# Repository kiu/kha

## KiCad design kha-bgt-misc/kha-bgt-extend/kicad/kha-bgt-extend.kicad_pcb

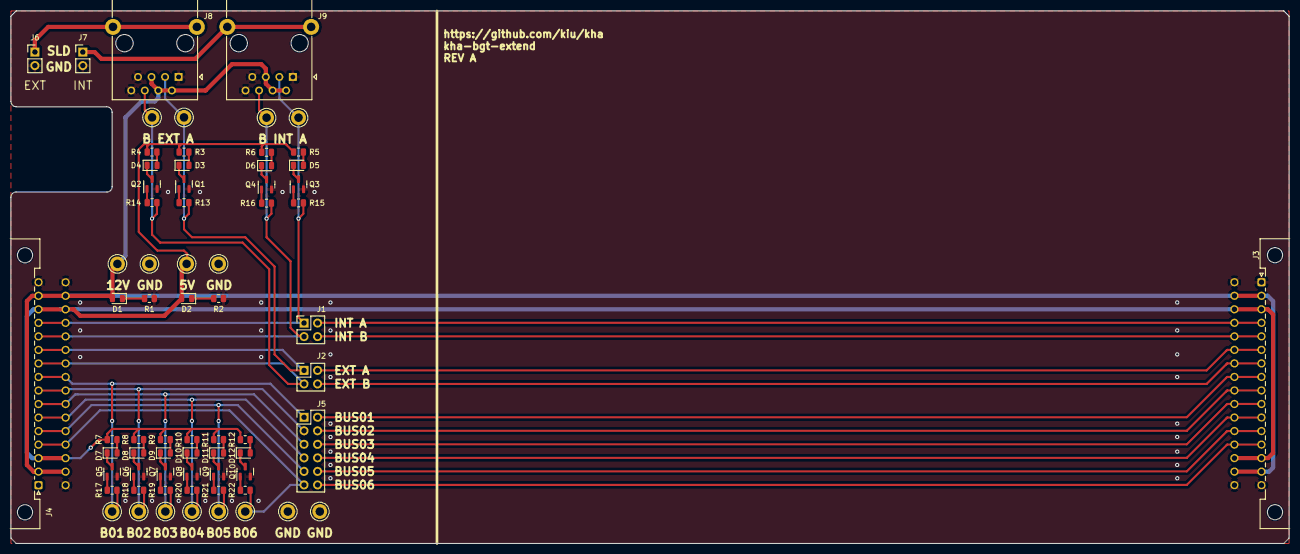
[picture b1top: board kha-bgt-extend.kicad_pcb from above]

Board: 2 copper layers, 240.0 x 100.0 mm, 69 parts (0 on the bottom side), 57 nets.

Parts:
D1, D2: green; LED_0805_2012Metric
D3, D4, D5, D6, D7, D8, D9, D10, D11, D12: yellow; LED_0805_2012Metric
J1, J2: Conn_02x02_Odd_Even; PinHeader_2x02_P2.54mm_Vertical
J3, J4: DIN41612_02x16_AC; DIN41612_C2_2x16_Male_Horizontal_THT
J5: Conn_02x06_Odd_Even; PinHeader_2x06_P2.54mm_Vertical
J6, J7: Conn_01x02; PinHeader_1x02_P2.54mm_Vertical
J8, J9: RJ45_Shielded; GDLX-S-88K
Q1, Q2, Q3, Q4, Q5, Q6, Q7, Q8, Q9, Q10: DMG2302U; SOT-23
R1, R2, R3, R4, R5, R6, R7, R8, R9, R10, R11, R12: R; R_0805_2012Metric
R13, R14, R15, R16, R17, R18, R19, R20, R21, R22: 10R; R_0805_2012Metric
TP1, TP2, TP3, TP4, TP5, TP6, TP7, TP8, TP9, TP10, TP11, TP12, TP13, TP14, TP15, TP16: TestPoint; TestPoint_Keystone_5010-5014_Multipurpose

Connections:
+5V: D2.2 (A), J3.a3, J3.a14, J3.c3, J3.c14, J4.a3, J4.a14, J4.c3, J4.c14, R3.2, R4.2, R5.2, R6.2, R7.2, R8.2, R9.2, R10.2, R11.2, R12.2, TP2.1
+12V: D1.2 (A), J3.a2, J3.a15, J3.c2, J3.c15, J4.a2, J4.a15, J4.c2, J4.c15, J8.2, J8.4, J8.5, J9.2, J9.4, J9.5, TP1.1
C_BUS01: J4.a9, J4.c9, J5.1, R17.2, TP11.1
C_BUS02: J4.a8, J4.c8, J5.3, R18.2, TP12.1
C_BUS03: J4.a7, J4.c7, J5.5, R19.2, TP13.1
C_BUS04: J4.a6, J4.c6, J5.7, R20.2, TP14.1
C_BUS05: J4.a5, J4.c5, J5.9, R21.2, TP15.1
C_BUS06: J4.a4, J4.c4, J5.11, R22.2, TP16.1
C_RS485_A: J2.1, J4.a11, J4.c11, J8.3, R13.2, TP7.1
C_RS485_B: J2.3, J4.a10, J4.c10, J8.6, R14.2, TP8.1
C_RS485_INT_A: J1.1, J4.a13, J4.c13, J9.3, R15.2, TP9.1
C_RS485_INT_B: J1.3, J4.a12, J4.c12, J9.6, R16.2, TP10.1
GND: J3.a1, J3.a16, J3.c1, J3.c16, J4.a16, J4.c1, J4.c16, J6.2, J7.2, J8.1, J8.7, J8.8, J9.1, J9.7, J9.8, Q1.2 (S), Q2.2 (S), Q3.2 (S), Q4.2 (S), Q5.2 (S), Q6.2 (S), Q7.2 (S), Q8.2 (S), Q9.2 (S), Q10.2 (S), R1.1, R2.1, TP3.1, TP4.1, TP5.1, TP6.1
unnamed: D1.1 (K), R1.2
unnamed: D2.1 (K), R2.2
unnamed: D3.2 (A), R3.1
unnamed: D3.1 (K), Q1.3 (D)
unnamed: D4.2 (A), R4.1
unnamed: D4.1 (K), Q2.3 (D)
unnamed: D5.2 (A), R5.1
unnamed: D5.1 (K), Q3.3 (D)
unnamed: D6.2 (A), R6.1
unnamed: D6.1 (K), Q4.3 (D)
unnamed: D7.2 (A), R7.1
unnamed: D7.1 (K), Q5.3 (D)
unnamed: D8.2 (A), R8.1
unnamed: D8.1 (K), Q6.3 (D)
unnamed: D9.2 (A), R9.1
unnamed: D9.1 (K), Q7.3 (D)
unnamed: D10.2 (A), R10.1
unnamed: D10.1 (K), Q8.3 (D)
unnamed: D11.2 (A), R11.1
unnamed: D11.1 (K), Q9.3 (D)
unnamed: D12.2 (A), R12.1
unnamed: D12.1 (K), Q10.3 (D)
unnamed: J6.1, J8.SH
unnamed: J7.1, J9.SH
unnamed: Q1.1 (G), R13.1
unnamed: Q2.1 (G), R14.1
unnamed: Q3.1 (G), R15.1
unnamed: Q4.1 (G), R16.1
unnamed: Q5.1 (G), R17.1
unnamed: Q6.1 (G), R18.1
unnamed: Q7.1 (G), R19.1
unnamed: Q8.1 (G), R20.1
unnamed: Q9.1 (G), R21.1
unnamed: Q10.1 (G), R22.1
R_BUS01: J3.a8, J3.c8, J5.2
R_BUS02: J3.a9, J3.c9, J5.4
R_BUS03: J3.a10, J3.c10, J5.6
R_BUS04: J3.a11, J3.c11, J5.8
R_BUS05: J3.a12, J3.c12, J5.10
R_BUS06: J3.a13, J3.c13, J5.12
R_RS485_A: J2.2, J3.a6, J3.c6
R_RS485_B: J2.4, J3.a7, J3.c7
R_RS485_INT_A: J1.2, J3.a4, J3.c4
R_RS485_INT_B: J1.4, J3.a5, J3.c5

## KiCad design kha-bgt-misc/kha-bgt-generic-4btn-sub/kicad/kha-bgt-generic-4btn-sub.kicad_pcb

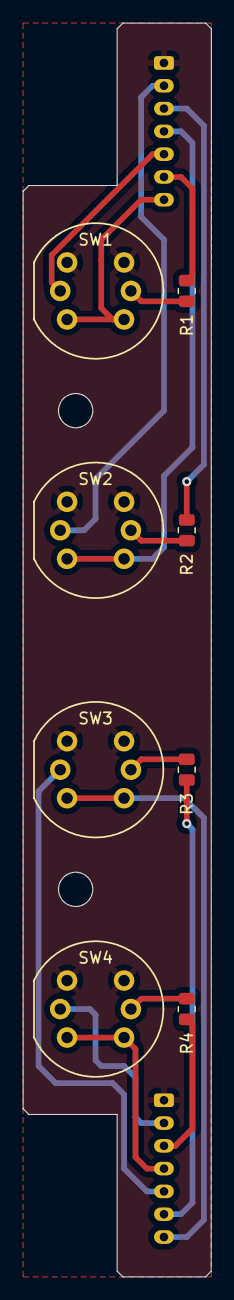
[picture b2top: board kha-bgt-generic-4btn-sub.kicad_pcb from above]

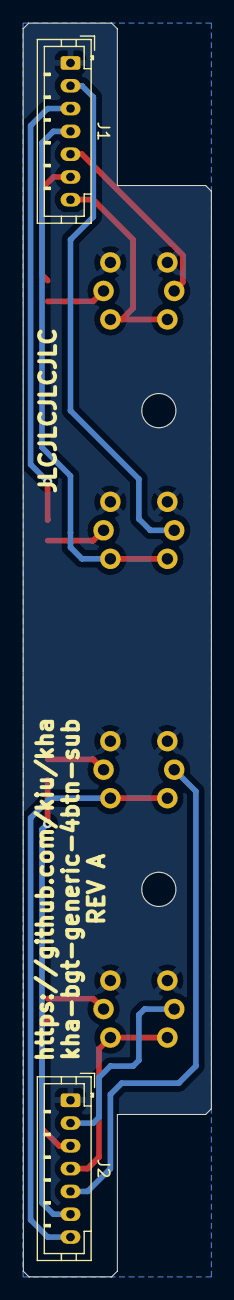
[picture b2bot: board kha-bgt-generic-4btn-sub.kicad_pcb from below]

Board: 2 copper layers, 16.5 x 110.0 mm, 10 parts (2 on the bottom side), 17 nets.

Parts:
J1, J2: Conn_01x07; JST_PH_B7B-PH-K_1x07_P2.00mm_Vertical
R1, R2, R3, R4: R; R_0805_2012Metric
SW1, SW2, SW3, SW4: KS01-BL

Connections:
GND: J1.1, J2.1, SW1.2, SW2.2, SW3.2, SW4.2
unnamed: J1.2, SW2.6
unnamed: J1.3, R2.1
unnamed: J1.4, SW2.1
unnamed: J1.5, SW1.6
unnamed: J1.6, R1.1
unnamed: J1.7, SW1.1
unnamed: J2.2, SW4.6
unnamed: J2.3, R4.1
unnamed: J2.4, SW4.1
unnamed: J2.5, SW3.6
unnamed: J2.6, R3.1
unnamed: J2.7, SW3.1
unnamed: R1.2, SW1.5
unnamed: R2.2, SW2.5
unnamed: R3.2, SW3.5
unnamed: R4.2, SW4.5

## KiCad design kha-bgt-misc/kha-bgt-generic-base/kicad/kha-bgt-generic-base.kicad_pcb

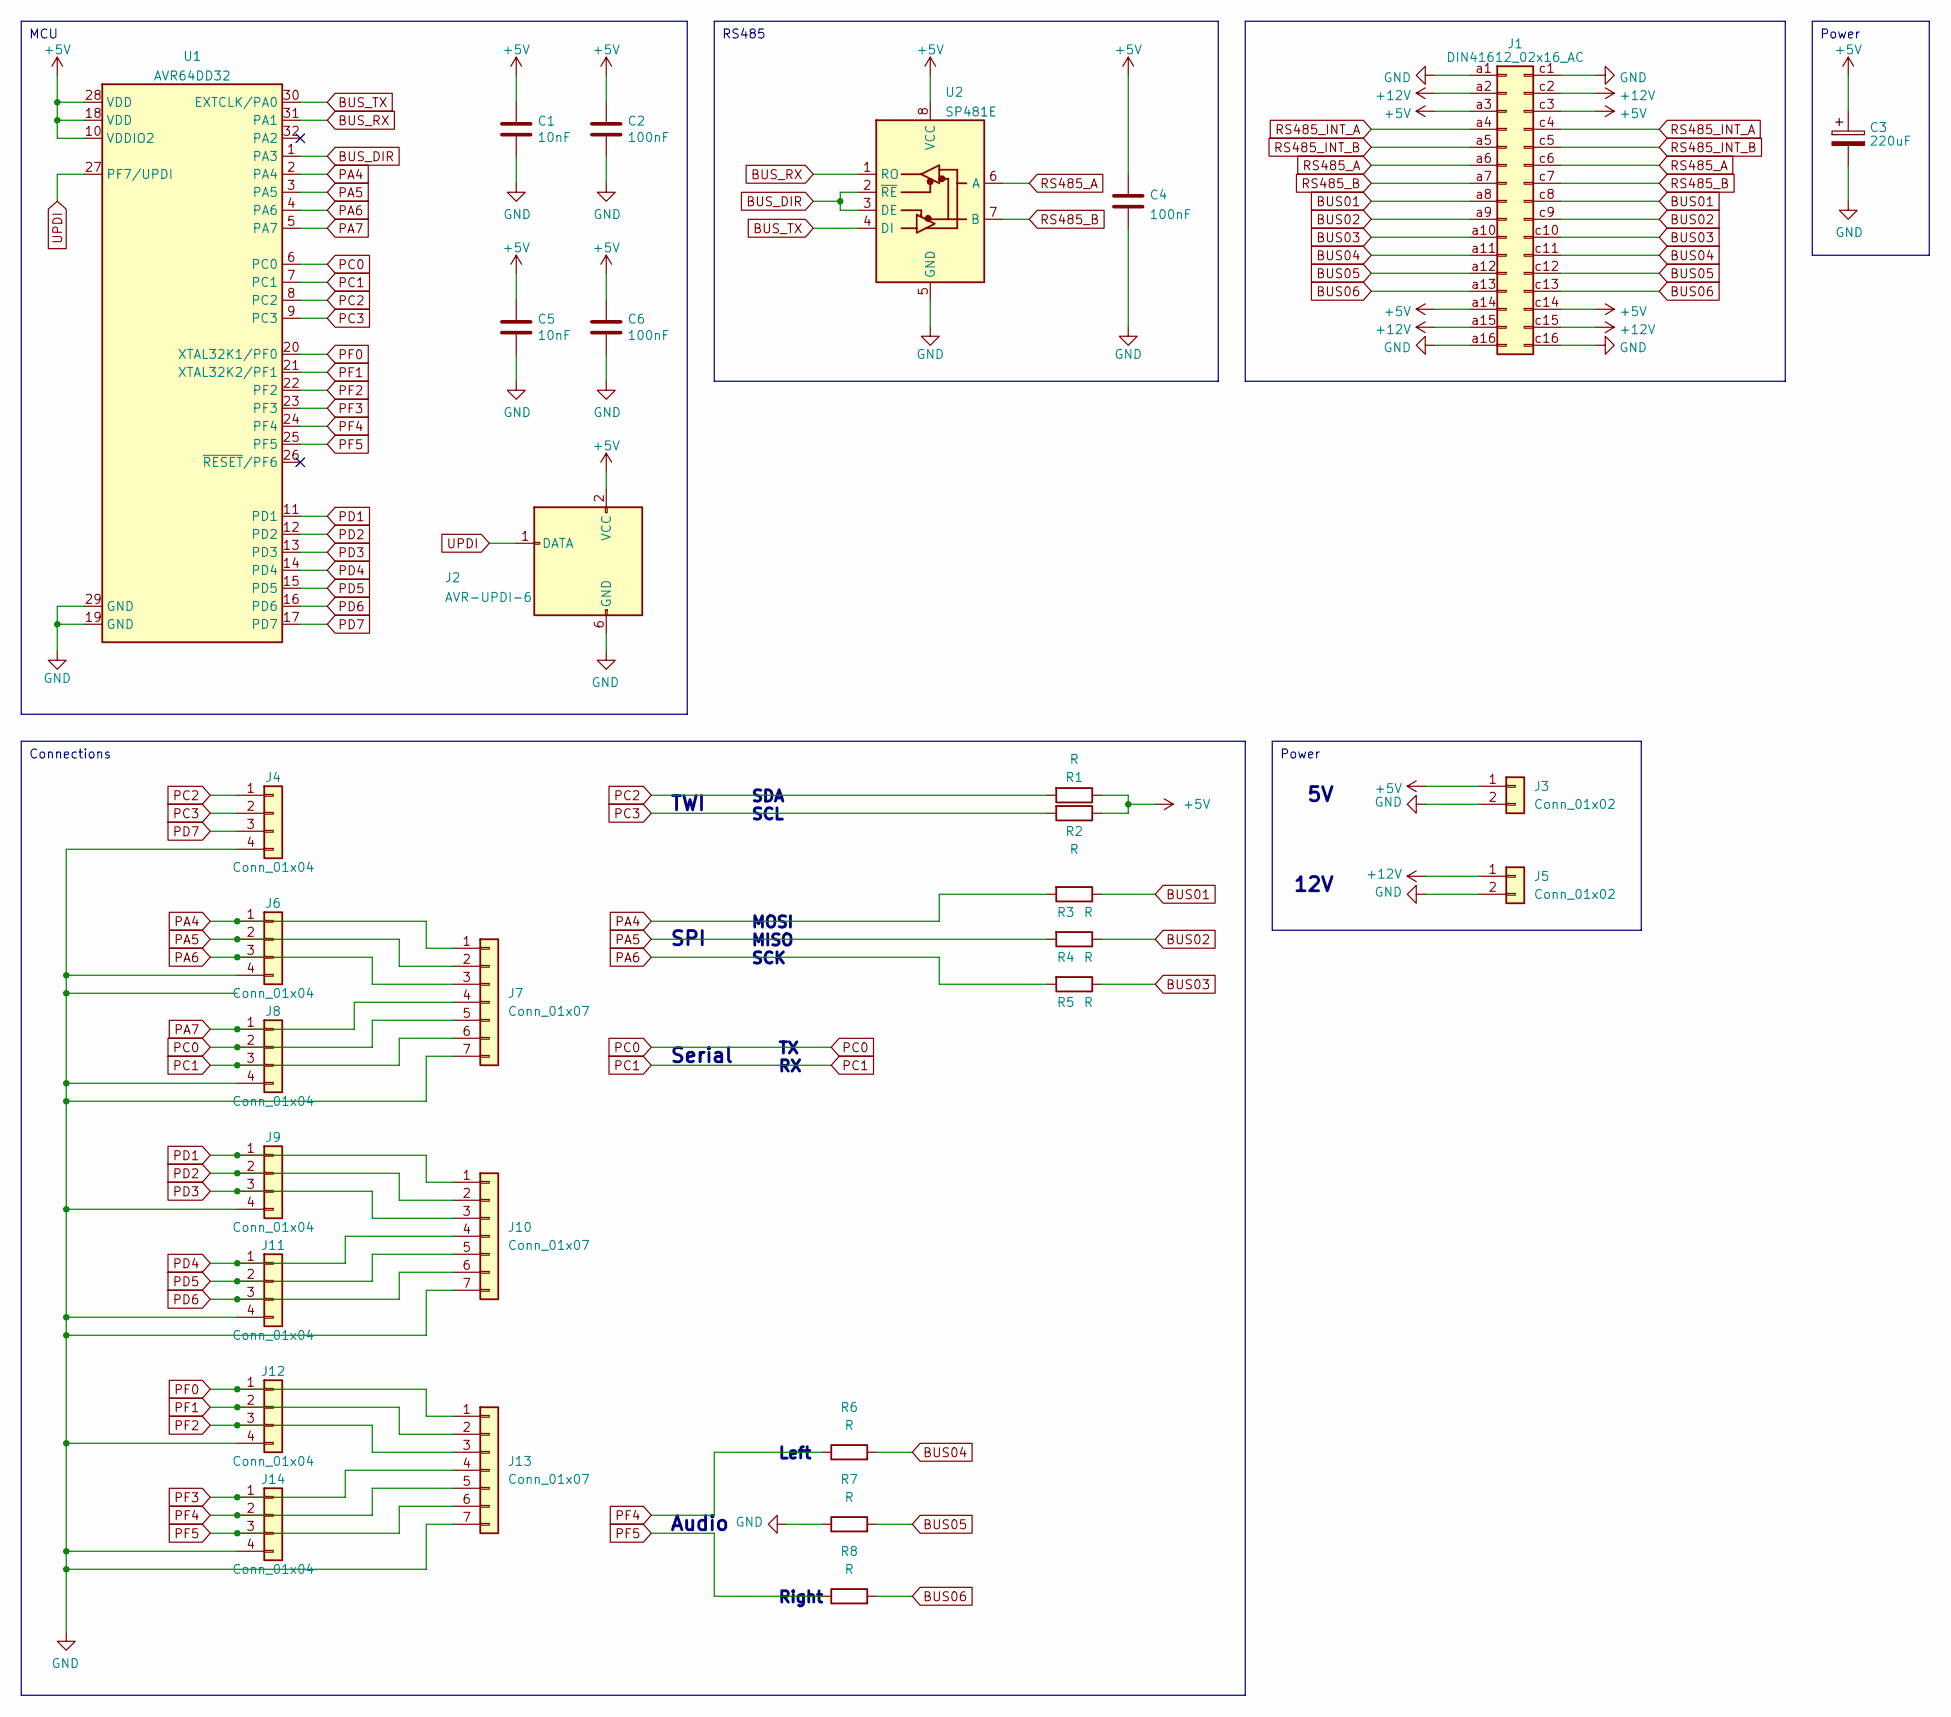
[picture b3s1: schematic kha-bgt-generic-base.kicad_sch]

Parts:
C1, C5: 10nF; C_0805_2012Metric
C2, C4, C6: 100nF; C_0805_2012Metric
C3: 220uF; CP_EIA-6032-28_Kemet-C
J1: DIN41612_02x16_AC; DIN41612_C2_2x16_Male_Horizontal_THT
J2: AVR-UPDI-6; eAVR6-UPDI-F
J3, J5: Conn_01x02; JST_PH_B2B-PH-K_1x02_P2.00mm_Vertical
J4, J6, J8, J9, J11, J12, J14: Conn_01x04; JST_PH_B4B-PH-K_1x04_P2.00mm_Vertical
J7, J10, J13: Conn_01x07; JST_PH_B7B-PH-K_1x07_P2.00mm_Vertical
R1, R2, R3, R4, R5, R6, R7, R8: R; R_0805_2012Metric
U1: AVR64DD32; TQFP-32_7x7mm_P0.8mm
U2: SP481E; SOIC-8_3.9x4.9mm_P1.27mm

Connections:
+5V: C1.1, C2.1, C3.1, C4.1, C5.1, C6.1, J1.a3, J1.a14, J1.c3, J1.c14, J2.2 (VCC), J3.1, R1.1, R2.1, U1.10 (VDDIO2), U1.18 (VDD), U1.28 (VDD), U2.8 (VCC)
+12V: J1.a2, J1.a15, J1.c2, J1.c15, J5.1
BUS01: J1.a8, J1.c8, R3.1
BUS02: J1.a9, J1.c9, R4.1
BUS03: J1.a10, J1.c10, R5.1
BUS04: J1.a11, J1.c11, R6.2
BUS05: J1.a12, J1.c12, R7.2
BUS06: J1.a13, J1.c13, R8.2
BUS_DIR: U1.1 (PA3), U2.2 (~RE), U2.3 (DE)
BUS_RX: U1.31 (PA1), U2.1 (RO)
BUS_TX: U1.30 (EXTCLK/PA0), U2.4 (DI)
GND: C1.2, C2.2, C3.2, C4.2, C5.2, C6.2, J1.a1, J1.a16, J1.c1, J1.c16, J2.6 (GND), J3.2, J4.4, J5.2, J6.4, J7.7, J8.4, J9.4, J10.7, J11.4, J12.4, J13.7, J14.4, R7.1, U1.19 (GND), U1.29 (GND), U2.5 (GND)
PA4: J6.1, J7.1, R3.2, U1.2 (PA4)
PA5: J6.2, J7.2, R4.2, U1.3 (PA5)
PA6: J6.3, J7.3, R5.2, U1.4 (PA6)
PA7: J7.4, J8.1, U1.5 (PA7)
PC0: J7.5, J8.2, U1.6 (PC0)
PC1: J7.6, J8.3, U1.7 (PC1)
PC2: J4.1, R1.2, U1.8 (PC2)
PC3: J4.2, R2.2, U1.9 (PC3)
PD1: J9.1, J10.1, U1.11 (PD1)
PD2: J9.2, J10.2, U1.12 (PD2)
PD3: J9.3, J10.3, U1.13 (PD3)
PD4: J10.4, J11.1, U1.14 (PD4)
PD5: J10.5, J11.2, U1.15 (PD5)
PD6: J10.6, J11.3, U1.16 (PD6)
PD7: J4.3, U1.17 (PD7)
PF0: J12.1, J13.1, U1.20 (XTAL32K1/PF0)
PF1: J12.2, J13.2, U1.21 (XTAL32K2/PF1)
PF2: J12.3, J13.3, U1.22 (PF2)
PF3: J13.4, J14.1, U1.23 (PF3)
PF4: J13.5, J14.2, R6.1, U1.24 (PF4)
PF5: J13.6, J14.3, R8.1, U1.25 (PF5)
RS485_A: J1.a6, J1.c6, U2.6 (A)
RS485_B: J1.a7, J1.c7, U2.7 (B)
RS485_INT_A: J1.a4, J1.c4
RS485_INT_B: J1.a5, J1.c5
UPDI: J2.1 (DATA), U1.27 (PF7/UPDI)

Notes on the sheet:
Connections
Power
RS485
MCU
SDA
Right
TWI
MISO
SCL
Serial
Audio
SPI
12V
SCK
Left
MOSI

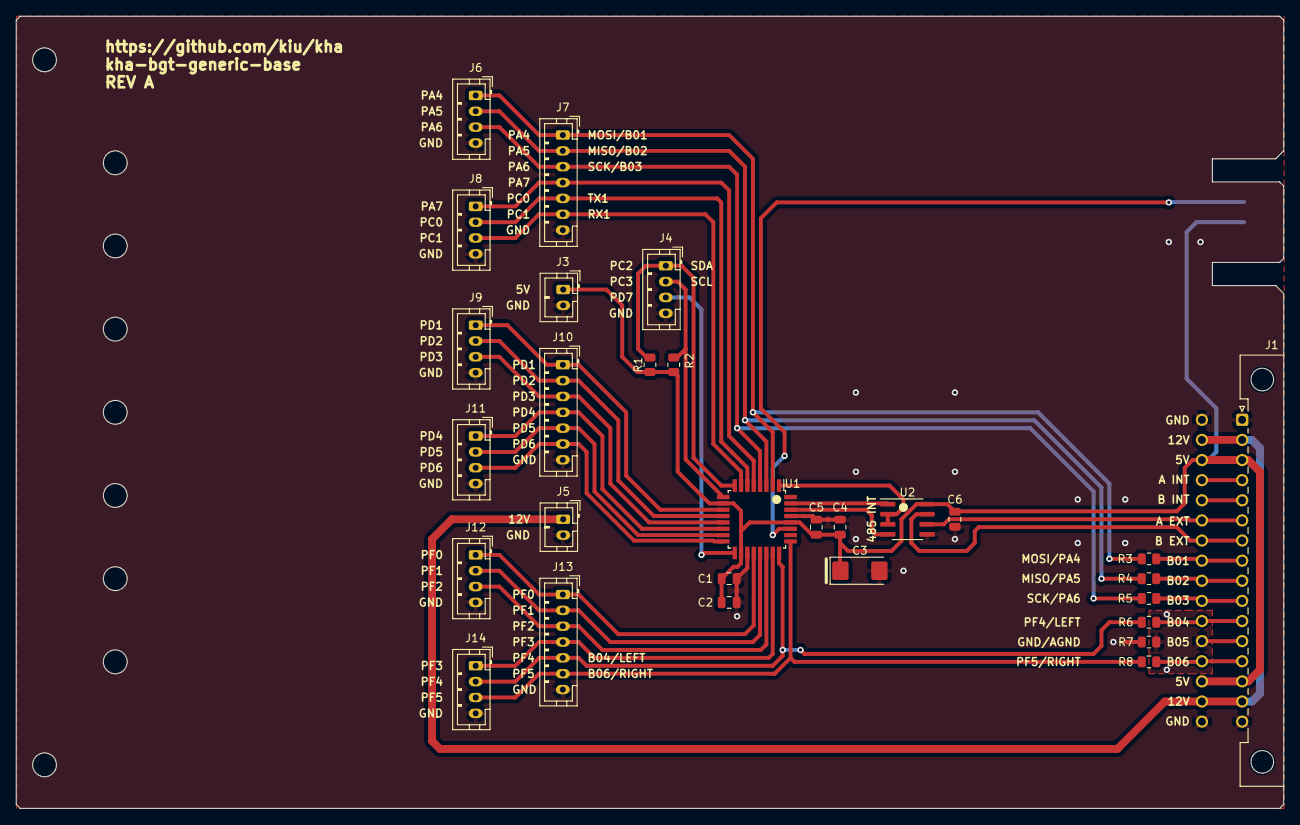
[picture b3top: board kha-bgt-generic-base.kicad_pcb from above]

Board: 2 copper layers, 160.0 x 100.0 mm, 30 parts (1 on the bottom side), 38 nets.

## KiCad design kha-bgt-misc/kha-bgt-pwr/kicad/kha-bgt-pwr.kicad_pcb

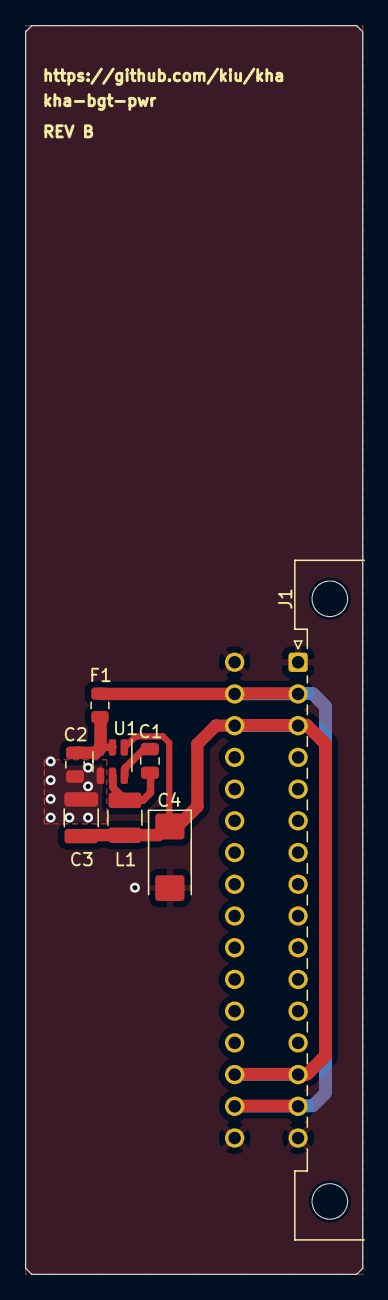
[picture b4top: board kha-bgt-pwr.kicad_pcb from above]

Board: 2 copper layers, 27.0 x 100.0 mm, 8 parts (0 on the bottom side), 6 nets.

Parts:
C1: 100nF; C_0805_2012Metric
C2: 10uF; C_0805_2012Metric
C3: 47uF; C_1210_3225Metric
C4: 220uF; CP_EIA-6032-28_Kemet-C
F1: Polyfuse; Fuse_0805_2012Metric
J1: DIN41612_02x16_AC; DIN41612_C2_2x16_Male_Horizontal_THT
L1: 4.7uH; L_1210_3225Metric
U1: AP63205WU; TSOT-23-6

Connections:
+5V: C3.1, C4.1, J1.a3, J1.a14, J1.c3, J1.c14, L1.2, U1.1 (FB)
+12V: F1.2, J1.a2, J1.a15, J1.c2, J1.c15
GND: C2.1, C3.2, C4.2, J1.a1, J1.a16, J1.c1, J1.c16, U1.4 (GND)
unnamed: C1.2, U1.6 (BST)
unnamed: C2.2, F1.1, U1.2 (EN), U1.3 (IN)
unnamed: C1.1, L1.1, U1.5 (SW)
